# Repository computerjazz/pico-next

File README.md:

# picopi

Simple connected toys built from a single action — turn a knob, press a button, flip a switch.

Each toy is a small wooden box with one big, satisfying control on top. WiFi-enabled ESP32 modules handle the electronics; this repo is the web app and backend that ties them together.

## Origin

Picopi started as a sandbox — a place to explore modern Next.js with Server Actions and React Server Components, and to figure out how to self-host the whole stack on a Raspberry Pi.

From there it grew into something much more physical. ESP32 modules, custom PCBs, woodworking, product design — all in service of one goal: building meaningful connected experiences for kids. Not apps on screens, but real objects with weight and texture that do one thing well.

**sh0rtwave** is the one that struck a chord. A little answering machine for voice messages between kids and the people who love them. Press the button, leave a message. When the light blinks, someone left one for you. The recordings pile up over time into a collection of audio I'll cherish forever.

## Toys

| Route           | Toy              | Action        | What it does                                                       |
| --------------- | ---------------- | ------------- | ------------------------------------------------------------------ |
| `/shortwave`    | **sh0rtwave**    | Push a button | Trade voice messages — no screens attached                         |
| `/toggle`       | **toggle**       | Flip a switch | Keep two toggles in sync from afar; compete on the leaderboard     |
| `/hidden-radio` | **hidden radio** | Turn a knob   | Discover what's hiding in the FM spectrum off the usual radio dial |

Firmware for each device lives under `esp32/`.

## Core technologies

### Web app

- **[Next.js 16](https://nextjs.org)** — App Router, React Server Components, and Server Actions
- **[React 19](https://react.dev)**
- **[TypeScript](https://www.typescriptlang.org)**
- **[Tailwind CSS 4](https://tailwindcss.com)**
- **[Motion](https://motion.dev)** — UI animations

### Backend & data

- **[PostgreSQL](https://www.postgresql.org)** with **[Drizzle ORM](https://orm.drizzle.team)** — devices, recordings, users, toggle groups, and more
- **[Redis](https://redis.io)** — pub/sub for routing real-time commands to connected clients
- **Custom Node server** (`server.ts`) — Next.js request handler plus a WebSocket server for live device communication
- **[Auth.js / NextAuth](https://authjs.dev)** — Google sign-in and session management
- **[Zod](https://zod.dev)** — runtime validation for API payloads and WebSocket messages
- **ffmpeg** — audio transcoding and processing (recordings, answering-machine playback)
- **[Sharp](https://sharp.pixelplumbing.com)** + **[Tesseract.js](https://tesseract.projectnaptha.com)** — image preprocessing and OCR (e.g. inbound mail parsing) for display on my TRMNL

### Hardware

- **[ESP32](https://www.espressif.com/en/products/socs/esp32)** (ESP32-S3) — WiFi, I2S audio, OTA firmware updates
- **Arduino / C++** firmware in `esp32/shortwave`, `esp32/toggle`, and `esp32/knob`
- **KiCad** PCB designs (e.g. `esp32/shortwave/sh0rtwave_pcb/`)

### Infrastructure & hosting

The whole stack runs self-hosted on a **Raspberry Pi**, deployed and managed through **[Coolify](https://coolify.io)**. The app ships as a **Docker** image (multi-stage build; production image includes `ffmpeg`).

| Layer           | Tool                                                                                                 | Role                                                                       |
| --------------- | ---------------------------------------------------------------------------------------------------- | -------------------------------------------------------------------------- |
| Compute         | Raspberry Pi + Coolify                                                                               | Self-hosted app platform                                                   |
| Containers      | Docker                                                                                               | Build, ship, and run the Next.js app + custom server                       |
| Database        | PostgreSQL                                                                                           | Primary data store (devices, recordings, users, toggle groups)             |
| Cache / pub-sub | Redis                                                                                                | Real-time command routing to WebSocket clients                             |
| Private network | [Tailscale](https://tailscale.com)                                                                   | Secure mesh VPN — access the Pi and services without exposing ports        |
| Public ingress  | [Cloudflare Tunnels](https://developers.cloudflare.com/cloudflare-one/connections/connect-networks/) | Expose the app to the internet (and ESP32 devices) without port forwarding |

### Integrations

- **Web Push** — notifications when new messages arrive
- **Gmail API** — inbound message processing
- **Telegram** — device channel integration
- **Google OAuth** — sign-in and API access

## Project structure

```
app/           Next.js pages, components, server actions, and API routes
db/            Drizzle schema and database client
esp32/         Device firmware and PCB files
lib/           Shared utilities (auth, redis, websocket, push, etc.)
scripts/       CLI helpers (Gmail auth, token generation, DB seeding)
server.ts      Custom HTTP + WebSocket server for production
drizzle/       Database migrations
public/        Static assets and OTA firmware binaries
```

## Getting started

### Prerequisites

- Node.js 20+
- PostgreSQL
- Redis

### Development

```bash
npm install
npm run dev
```

Open [http://localhost:3000](http://localhost:3000).

### Production build

In production the app runs on a Raspberry Pi via Coolify, behind a Cloudflare Tunnel, with PostgreSQL and Redis as managed services on the same host.

```bash
npm run build          # Next.js build
npm run build:server   # Bundle custom server
npm run build:release  # Build + run with .env.local
```

Or build the Docker image directly:

```bash
docker build -t picopi .
docker run -p 3000:3000 picopi
```

### Environment

Copy and configure environment variables for your local setup (database URL, Redis, auth secrets, API keys). See `.env.local` and the `env.h.example` files under `esp32/` for device-side credentials.

### Database

```bash
npx drizzle-kit migrate
```

## License

Private — not open source.

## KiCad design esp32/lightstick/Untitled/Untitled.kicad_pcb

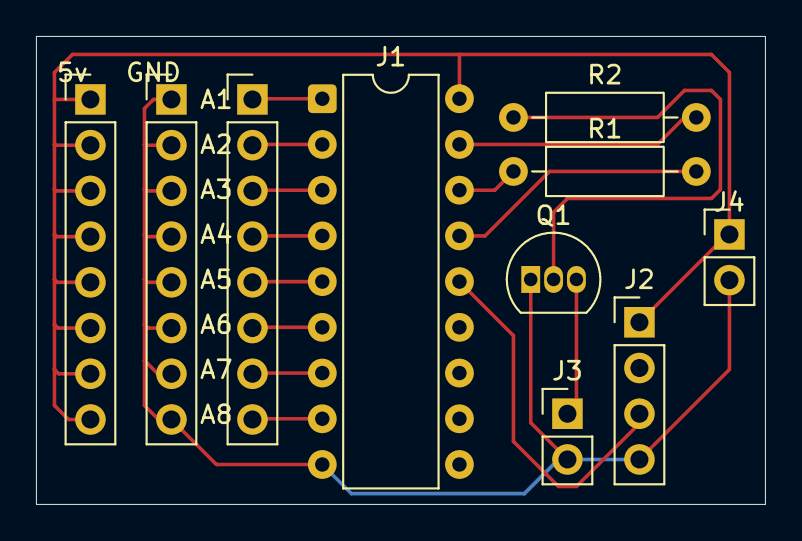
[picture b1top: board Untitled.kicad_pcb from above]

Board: 2 copper layers, 40.5 x 26.0 mm, 10 parts (0 on the bottom side), 16 nets.

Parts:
5v: Conn_01x08_Pin; PinHeader_1x08_P2.54mm_Vertical
A1: Conn_01x08_Pin; PinHeader_1x08_P2.54mm_Vertical
GND: Conn_01x08_Pin; PinHeader_1x08_P2.54mm_Vertical
J1: Conn_02x09_Odd_Even; DIP-18_W7.62mm
J2: Conn_01x04_Pin; PinHeader_1x04_P2.54mm_Vertical
J3, J4: Conn_01x02_Pin; PinHeader_1x02_P2.54mm_Vertical
Q1: S8050; TO-92_Inline
R1: R_US 750k; R_Axial_DIN0207_L6.3mm_D2.5mm_P10.16mm_Horizontal
R2: R_US 1k; R_Axial_DIN0207_L6.3mm_D2.5mm_P10.16mm_Horizontal

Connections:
+5V: 5v.1, 5v.2, 5v.3, 5v.4, 5v.5, 5v.6, 5v.7, 5v.8, J1.18, J2.1, J4.1
GND: GND.1, GND.2, GND.3, GND.4, GND.5, GND.6, GND.7, GND.8, J1.9, J2.4, J3.2, J4.2, Q1.1 (E)
unnamed: A1.1, J1.1
unnamed: A1.2, J1.2
unnamed: A1.3, J1.3
unnamed: A1.4, J1.4
unnamed: A1.5, J1.5
unnamed: A1.6, J1.6
unnamed: A1.7, J1.7
unnamed: A1.8, J1.8
unnamed: J1.14, J2.3
unnamed: J1.15, R1.2
unnamed: J1.16, R1.1
unnamed: J1.17, R2.2
unnamed: J3.1, Q1.3 (C)
unnamed: Q1.2 (B), R2.1

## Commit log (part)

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2026-05-09 set lastSeenAt
2026-05-10 update audio
2026-05-11 fix top-level await build issue
2026-05-11 comment out
2026-05-11 set last seen
2026-05-11 icons
2026-05-11 logging
2026-05-11 change base url
2026-05-11 remove noisy logs
2026-05-11 update fetchAudio
2026-05-11 load src
2026-05-11 update try/catch
2026-05-11 recording provider
2026-05-11 only pause other recordings
2026-05-12 add transcribe
2026-05-12 add answering machine/device indicators
2026-05-12 add logging
2026-05-12 remove dev null
2026-05-12 logs
2026-05-12 whisper bin, update schema
2026-05-12 save transcription if success
2026-05-12 list style
2026-05-12 update recordings
2026-05-12 cleanup
2026-05-12 attempt transcribe
2026-05-12 style
2026-05-12 refactor recording
2026-05-12 fix output path
2026-05-12 fix duration check
2026-05-12 prefer processed audio
2026-05-12 date formatting
2026-05-12 process next
2026-05-12 rename
2026-05-13 simplify
2026-05-13 migrate
2026-05-13 keep track of messages
2026-05-13 update messages
2026-05-14 active job state
2026-05-14 update tsc build script
2026-05-14 move to env
2026-05-14 update vol input
2026-05-14 better query
2026-05-14 build server
2026-05-14 subscriber
2026-05-15 record message from web
2026-05-15 load jquery before interactive
2026-05-15 light/dark first pass
2026-05-15 revalidate
2026-05-16 colors
2026-05-16 theme
2026-05-16 most recent last sort
2026-05-16 scroll, kinda
2026-05-16 fix scroll
2026-05-16 scroll to bottom
2026-05-17 fade in on load
2026-05-17 hide device details
2026-05-17 scroll
2026-05-17 add gap
2026-05-18 add shortwave page
2026-05-18 add pages
2026-05-18 homepage
2026-05-18 icon
2026-05-18 update header
2026-05-18 title
2026-05-18 update icon
2026-05-18 fewer os
2026-05-18 update naming
2026-05-18 remove ligatures
2026-05-18 banner
2026-05-19 copy
2026-05-19 hover
2026-05-19 optimize
2026-05-19 flex
2026-05-19 add toggle img
2026-05-19 text accent
2026-05-19 remove reducer
2026-05-19 img cache
2026-05-19 update drizzle, toggle
2026-05-19 images
2026-05-19 add key
2026-05-19 better hover
2026-05-19 fix name
2026-05-19 update toggle
2026-05-19 update 2026-05-19.2 bin
2026-05-19 corners
2026-05-19 z-index
2026-05-19 fix record btn
2026-05-19 add haptic
2026-05-20 move vibrate to top of fn
2026-05-20 manifest
2026-05-20 haptic, manifests
2026-05-20 subscribe
2026-05-20 push bones
2026-05-20 fix dup subscriptions
2026-05-20 send web push
2026-05-20 try pointer down
2026-05-20 fix env var
2026-05-20 chatId -> deviceId
2026-05-20 push sub action
2026-05-20 export type from lib
2026-05-20 export type
2026-05-20 update list
2026-05-20 button
2026-05-20 update favicon
2026-05-20 fix mask colors
2026-05-20 name input
2026-05-20 remove color
2026-05-20 restrict btn to owner
2026-05-20 refactor components
2026-05-20 autoscroll
2026-05-20 make public
2026-05-20 filter null
2026-05-20 heros
2026-05-20 vol pct
2026-05-21 add ota logs
2026-05-21 update bin
2026-05-21 fix failing ota chack
2026-05-21 throttle
2026-05-21 orderby
2026-05-21 hero
2026-05-26 schematic
2026-05-26 flip page
2026-05-26 spacing
2026-05-27 cads mobile
2026-05-29 knob
2026-06-01 sanitize
2026-06-01 pcb update, copy
2026-06-01 hero video
2026-06-04 update connection test
2026-06-04 add bin
2026-06-05 loosen schema
2026-06-05 update toggle bin
2026-06-05 move socket logic to lib
2026-06-05 add link
2026-06-05 update leaderboard
2026-06-05 better cleanup
2026-06-05 validate sockets via zod
2026-06-05 add download button
2026-06-05 readme, fix audio source
2026-06-06 log memory
2026-06-07 trigger state via ws
2026-06-07 fix version number
2026-06-07 separate tasks/harden
2026-06-09 share recordings
2026-06-09 do not wrap signin
2026-06-12 useSocket helper
2026-06-13 useSocket
2026-06-13 simplify sockets
2026-06-13 socket
2026-06-13 parse
2026-06-13 scroll into view
2026-06-13 type
2026-06-13 only autoscroll when not scrolled up
2026-06-13 update schematic
2026-06-14 add test
2026-06-14 tests
2026-06-18 add bones of share
2026-06-18 add device header
2026-06-18 remove isMenuOpen
2026-06-19 attempt fix OOM
2026-06-19 join page
2026-06-19 handle expiration
2026-06-19 only scroll after initial set
2026-06-19 fix share
2026-06-19 add toaster
2026-06-19 confirm dialog
2026-06-19 toast
2026-06-19 check share
2026-06-19 check access
2026-06-19 share helper
2026-06-20 generateMetadata
2026-06-20 share confirm
2026-06-20 add transcript
2026-06-20 update binaries w new url
2026-06-21 add toggle group reset
2026-06-21 remove outline
2026-06-22 tweak toggle logic, add tests
2026-06-22 scoreboard->leaderboard
2026-06-22 update confirm dialog
2026-06-22 leaderboard
2026-06-22 remove events summary
2026-06-23 update schema, scoring logic
2026-06-23 remove deprecated
2026-06-23 migrate old toggles
2026-06-23 add isActive
2026-06-23 do not include in progress score in migration
2026-06-23 types, build
2026-06-24 3 player virtual
2026-06-24 fix command parse
2026-06-24 switch onChange
2026-06-25 init
2026-06-25 init device
2026-06-25 idiomatic routing
2026-06-25 fix scoring logic
2026-06-25 animate
2026-06-25 update row instead of storing each toggle
2026-06-26 update dev check
2026-06-26 better leaderboard
2026-06-26 fix types
2026-06-26 modifiers
2026-06-26 earlier bypass
2026-06-26 add isFocused hook
2026-06-26 switch color
2026-06-26 tweak device header styles
